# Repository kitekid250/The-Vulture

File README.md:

# The-Vulture
Work done on the robotic Vulture for Dana 147

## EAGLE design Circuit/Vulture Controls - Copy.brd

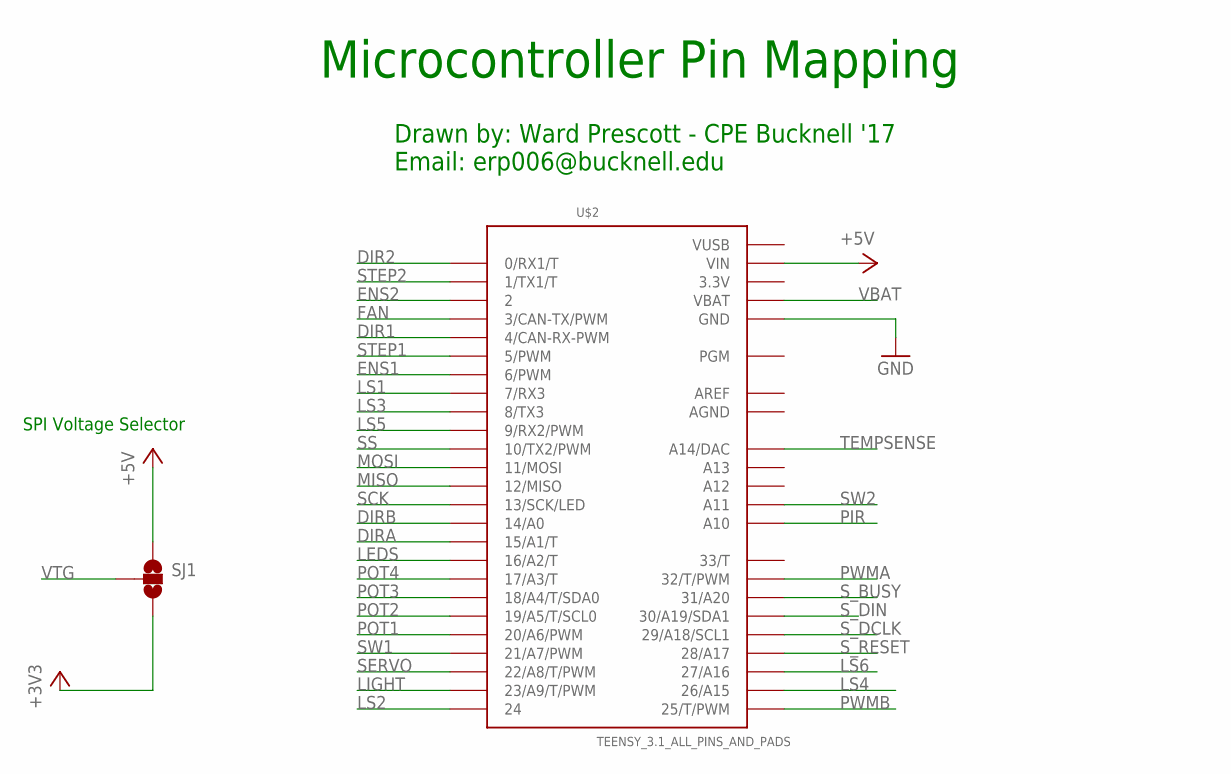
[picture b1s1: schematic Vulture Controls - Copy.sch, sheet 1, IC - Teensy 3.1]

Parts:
SJ1: JUMPER-PAD-3-NOFULL_BOX_SILK; PAD-JUMPER-3-NO_YES_SILK_FULL_BOX
U$2: TEENSY_3.1_ALL_PINS_AND_PADS; TEENSY_3.1_ALLPINS

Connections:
3.3V: U$2.3.3V, U$2.3.3V1 (3.3V), U$2.3.3V2 (3.3V)
+3V3: SJ1.3; also elsewhere on the board
+5V: SJ1.1, U$2.VIN; also elsewhere on the board
AGND: U$2.AGND
AREF: U$2.AREF
DIR1: U$2.4 (4/CAN-RX-PWM); also elsewhere on the board
DIR2: U$2.0 (0/RX1/T); also elsewhere on the board
DIRA: U$2.15/A1 (15/A1/T); also elsewhere on the board
DIRB: U$2.14/A0; also elsewhere on the board
ENS1: U$2.6 (6/PWM); also elsewhere on the board
ENS2: U$2.2; also elsewhere on the board
FAN: U$2.3 (3/CAN-TX/PWM); also elsewhere on the board
GND: U$2.GND, U$2.GND1 (GND), U$2.GND2 (GND); also elsewhere on the board
LEDS: U$2.16/A2 (16/A2/T); also elsewhere on the board
LIGHT: U$2.23/A9 (23/A9/T/PWM); also elsewhere on the board
LS1: U$2.7 (7/RX3); also elsewhere on the board
LS2: U$2.24; also elsewhere on the board
LS3: U$2.8 (8/TX3); also elsewhere on the board
LS4: U$2.26 (26/A15); also elsewhere on the board
LS5: U$2.9 (9/RX2/PWM); also elsewhere on the board
LS6: U$2.27 (27/A16); also elsewhere on the board
MISO: U$2.12 (12/MISO); also elsewhere on the board
MOSI: U$2.11 (11/MOSI); also elsewhere on the board
PIR: U$2.A10; also elsewhere on the board
POT1: U$2.20/A6 (20/A6/PWM); also elsewhere on the board
POT2: U$2.19/A5 (19/A5/T/SCL0); also elsewhere on the board
POT3: U$2.18/A4 (18/A4/T/SDA0); also elsewhere on the board
POT4: U$2.17/A3 (17/A3/T); also elsewhere on the board
PWMA: U$2.32 (32/T/PWM); also elsewhere on the board
PWMB: U$2.25 (25/T/PWM); also elsewhere on the board
SCK: U$2.13 (13/SCK/LED); also elsewhere on the board
SERVO: U$2.22/A8 (22/A8/T/PWM); also elsewhere on the board
SS: U$2.10 (10/TX2/PWM); also elsewhere on the board
STEP1: U$2.5 (5/PWM); also elsewhere on the board
STEP2: U$2.1 (1/TX1/T); also elsewhere on the board
SW1: U$2.21/A7 (21/A7/PWM); also elsewhere on the board
SW2: U$2.A11; also elsewhere on the board
S_BUSY: U$2.31 (31/A20); also elsewhere on the board
S_DCLK: U$2.29 (29/A18/SCL1); also elsewhere on the board
S_DIN: U$2.30 (30/A19/SDA1); also elsewhere on the board
S_RESET: U$2.28 (28/A17); also elsewhere on the board
TEMPSENSE: U$2.A14 (A14/DAC); also elsewhere on the board
VBAT: U$2.VBAT; also elsewhere on the board
VTG: SJ1.2; also elsewhere on the board
VUSB: U$2.VUSB

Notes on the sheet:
Microcontroller Pin Mapping
Drawn by: Ward Prescott - CPE Bucknell '17 Email: erp006@bucknell.edu
SPI Voltage Selector

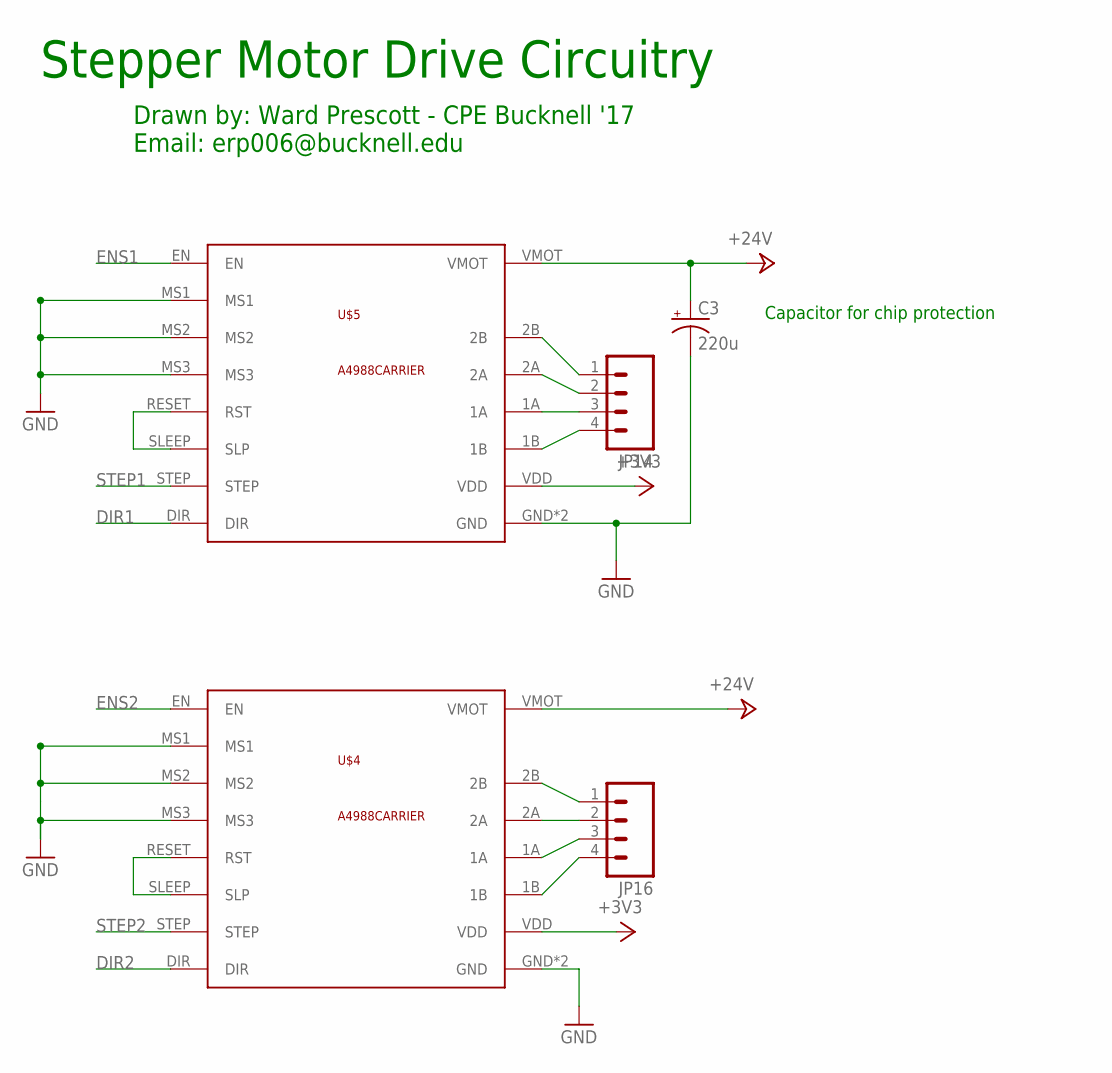
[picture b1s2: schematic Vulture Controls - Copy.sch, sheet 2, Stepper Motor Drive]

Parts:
C3: 220u; CPOL-RADIAL-1000UF-25V
JP14, JP16: M04POLAR_LOCK; MOLEX-1X4_LOCK
U$4, U$5: A4988CARRIER

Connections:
+3V3: U$4.VDD, U$5.VDD; also elsewhere on the board
+24V: C3.+, U$4.VMOT, U$5.VMOT; also elsewhere on the board
DIR1: U$5.DIR; also elsewhere on the board
DIR2: U$4.DIR; also elsewhere on the board
ENS1: U$5.EN; also elsewhere on the board
ENS2: U$4.EN; also elsewhere on the board
GND: C3.-, U$4.GND, U$4.GND2 (GND), U$4.MS1, U$4.MS2, U$4.MS3, U$5.GND, U$5.GND2 (GND), U$5.MS1, U$5.MS2, U$5.MS3; also elsewhere on the board
unnamed: JP14.1, U$5.2B
unnamed: JP14.2, U$5.2A
unnamed: JP14.3, U$5.1A
unnamed: JP14.4, U$5.1B
unnamed: JP16.1, U$4.2B
unnamed: JP16.2, U$4.2A
unnamed: JP16.3, U$4.1A
unnamed: JP16.4, U$4.1B
unnamed: U$5.RESET (RST), U$5.SLEEP (SLP)
unnamed: U$4.RESET (RST), U$4.SLEEP (SLP)
STEP1: U$5.STEP; also elsewhere on the board
STEP2: U$4.STEP; also elsewhere on the board

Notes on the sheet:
Capacitor for chip protection
Stepper Motor Drive Circuitry
Drawn by: Ward Prescott - CPE Bucknell '17 Email: erp006@bucknell.edu

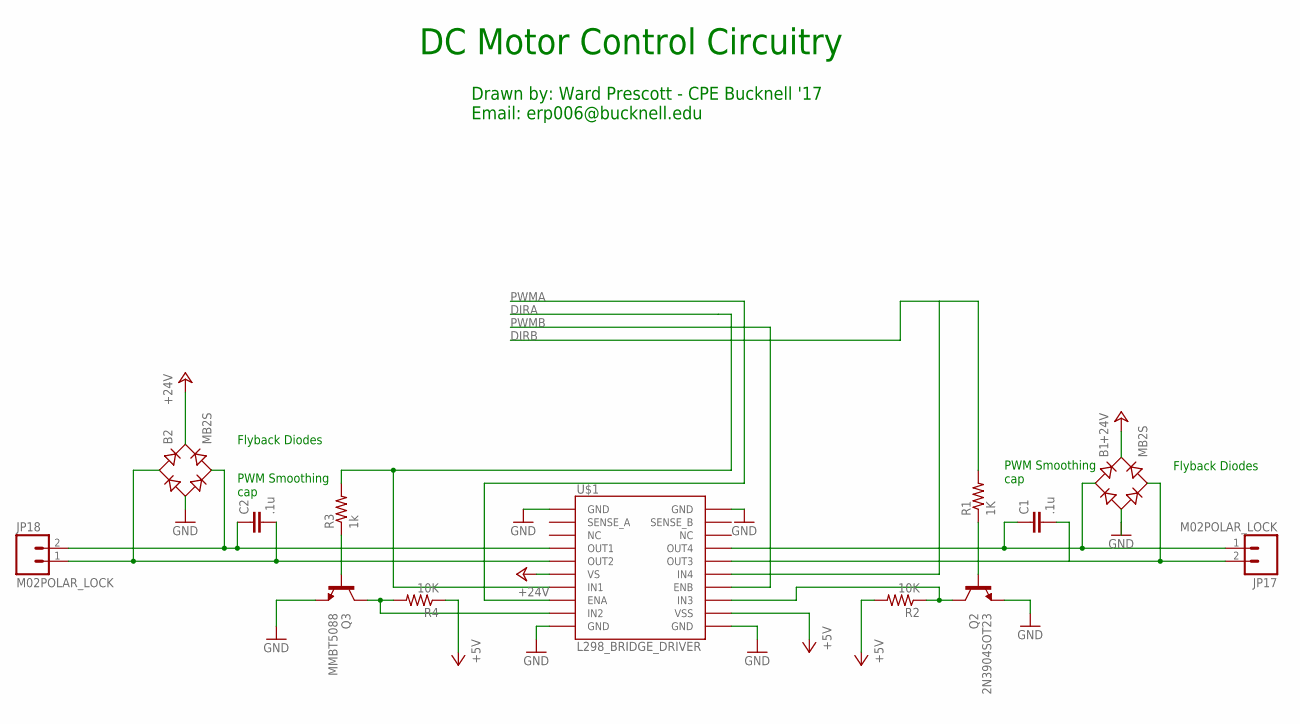
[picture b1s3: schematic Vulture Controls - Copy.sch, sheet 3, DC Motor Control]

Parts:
B1, B2: MB2S; SOIC-4
C1, C2: .1u; 1210
JP17, JP18: M02POLAR_LOCK; MOLEX-1X2_LOCK
Q2: 2N3904SOT23; SOT23
Q3: MMBT5088; SOT23
R1: 1K; 0805
R2, R4: 10K; 0603-RES
R3: 1k; 0805
U$1: L298_BRIDGE_DRIVER; POWERSO20

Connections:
+5V: R2.2, R4.1, U$1.12 (VSS); also elsewhere on the board
+24V: B1.+, B2.+, U$1.6 (VS); also elsewhere on the board
DIRA: R3.2, U$1.7 (IN1); also elsewhere on the board
DIRB: R1.2, U$1.15 (IN4); also elsewhere on the board
GND: B1.-, B2.-, Q2.2 (E), Q3.2 (E), U$1.1 (GND), U$1.10 (GND), U$1.11 (GND), U$1.20 (GND), U$1.P$1 (GND); also elsewhere on the board
unnamed: B2.~2 (AC2), C2.1, JP18.2, U$1.4 (OUT1)
unnamed: B2.~1 (AC1), C2.2, JP18.1, U$1.5 (OUT2)
unnamed: B1.~1 (AC1), C1.1, JP17.1, U$1.17 (OUT4)
unnamed: B1.~2 (AC2), C1.2, JP17.2, U$1.16 (OUT3)
unnamed: Q2.1 (B), R1.1
unnamed: Q2.3 (C), R2.1, U$1.13 (IN3)
unnamed: Q3.1 (B), R3.1
unnamed: Q3.3 (C), R4.2, U$1.9 (IN2)
PWMA: U$1.8 (ENA); also elsewhere on the board
PWMB: U$1.14 (ENB); also elsewhere on the board

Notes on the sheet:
Flyback Diodes
PWM Smoothing cap
DC Motor Control Circuitry
Drawn by: Ward Prescott - CPE Bucknell '17 Email: erp006@bucknell.edu

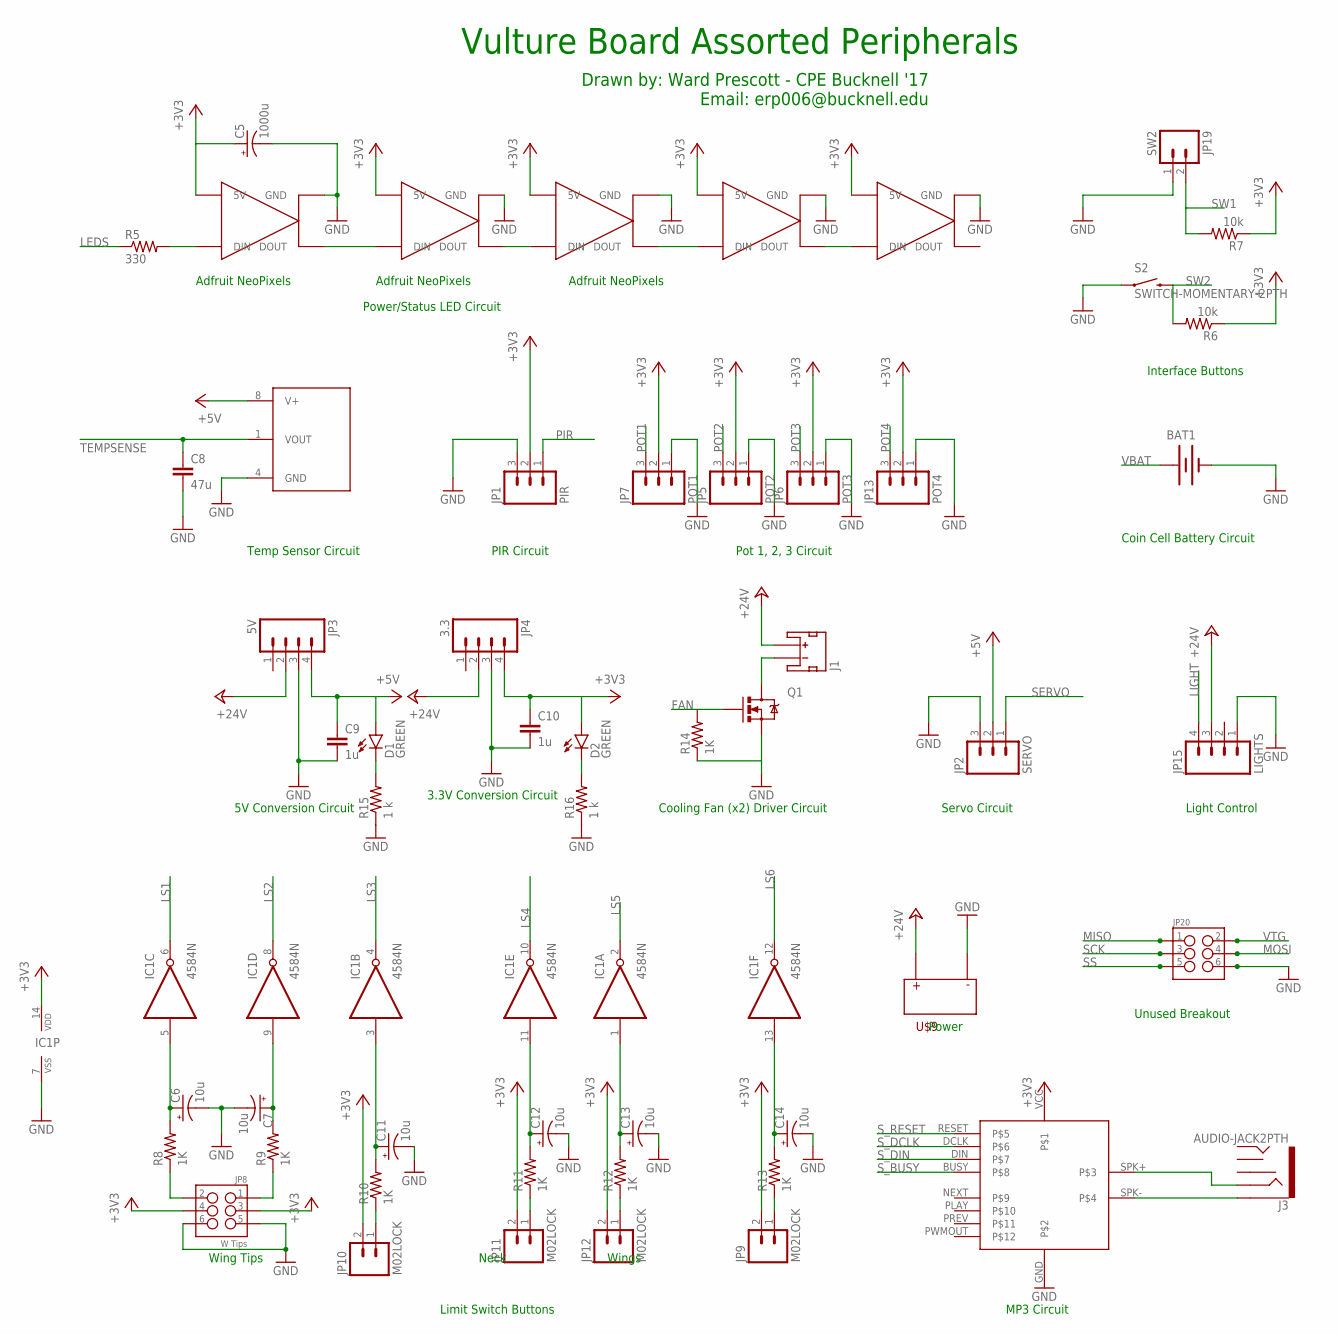
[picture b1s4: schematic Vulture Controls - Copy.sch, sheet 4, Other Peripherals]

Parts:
BAT1: BATTERY20PTH; BATTCOM_20MM_PTH
C5: 1000u; PANASONIC_G
C6, C7, C11, C12, C13, C14: 10u; PANASONIC_C
C8: 47u; 1206
C9, C10: 1u; 1206
D1, D2: GREEN; LED-1206
IC1: 4584N; DIL14
J1: JST_2MM_MALE; JST-2-SMD
J3: AUDIO-JACK2PTH; AUDIO-JACK
JP1: PIR; 1X03_LOCK_LONGPADS
JP2: SERVO; 1X03_LOCK_LONGPADS
JP3: 5V; 1X04_LOCK
JP4: 3.3; 1X04_LOCK
JP5: POT2; 1X03_LOCK_LONGPADS
JP6: POT3; 1X03_LOCK_LONGPADS
JP7: POT1; 1X03_LOCK_LONGPADS
JP8: W Tips; 2X3_POGO
JP9, JP10, JP11, JP12: M02LOCK; 1X02_LOCK
JP13: POT4; 1X03_LOCK_LONGPADS
JP15: LIGHTS; MOLEX-1X4_LOCK
JP19: SW2; 1X02_LOCK
JP20: M03X2POGO_PINS; 2X3_POGO
Q1: SSM3K329R,LF; SOT323
R5: 330; 0603-RES
R6, R7: 10k; 0603-RES
R8, R9, R10, R11, R12, R13, R14: 1K; 0805
R15, R16: 1 k; 0805
S2: SWITCH-MOMENTARY-2PTH; TACTILE-PTH
U$3: LM34; SO08
U$6, U$7, U$8, U$10, U$11: NEOPIXEL_THT
U$9: CONN_HDR_2POS_7.5MM_R/A_SLDR; MOLEXPOWER
U$12: WTV020SD-BRKOUT; WTVO20SD-BRKKOUT

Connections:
+3V3: C5.+, C10.1, D2.A, IC1.14 (VDD), JP1.2, JP4.4, JP5.2, JP6.2, JP7.2, JP8.P$3 (3), JP8.P$4 (4), JP9.2, JP10.2, JP11.2, JP12.2, JP13.2, R6.1, R7.1, U$6.5V, U$7.5V, U$8.5V, U$10.5V, U$11.5V, U$12.VCC; also elsewhere on the board
+5V: C9.1, D1.A, JP2.2, JP3.4, U$3.8 (V+); also elsewhere on the board
+24V: J1.2 (+), JP3.2, JP4.2, JP15.3, U$9.P$1, U$9.P$2; also elsewhere on the board
FAN: Q1.1 (G), R14.2; also elsewhere on the board
GND: BAT1.2 (-), C5.-, C6.-, C7.-, C8.2, C9.2, C10.2, C11.-, C12.-, C13.-, C14.-, IC1.7 (VSS), JP1.3, JP2.3, JP3.3, JP4.3, JP5.1, JP6.1, JP7.1, JP8.P$5 (5), JP8.P$6 (6), JP13.1, JP15.1, JP19.1, JP20.P$6 (6), Q1.2 (S), R14.1, R15.1, R16.1, S2.1, U$3.4 (GND), U$6.GND, U$7.GND, U$8.GND, U$9.P$3, U$9.P$4, U$10.GND, U$11.GND, U$12.GND; also elsewhere on the board
LEDS: R5.1; also elsewhere on the board
LIGHT: JP15.4; also elsewhere on the board
LS1: IC1.6 (O); also elsewhere on the board
LS2: IC1.8 (O); also elsewhere on the board
LS3: IC1.4 (O); also elsewhere on the board
LS4: IC1.10 (O); also elsewhere on the board
LS5: IC1.2 (O); also elsewhere on the board
LS6: IC1.12 (O); also elsewhere on the board
MISO: JP20.P$1 (1); also elsewhere on the board
MOSI: JP20.P$4 (4); also elsewhere on the board
N1: C6.+, IC1.5 (I), R8.2
N2: C7.+, IC1.9 (I), R9.2
N3: C11.+, IC1.3 (I), R10.2
N5: C13.+, IC1.1 (I), R12.2
N6: C14.+, IC1.13 (I), R13.2
unnamed: C12.+, IC1.11 (I), R11.2
unnamed: JP10.1, R10.1
unnamed: JP11.1, R11.1
unnamed: JP12.1, R12.1
unnamed: U$6.DOUT, U$7.DIN
unnamed: U$8.DOUT, U$10.DIN
unnamed: R5.2, U$6.DIN
unnamed: U$7.DOUT, U$8.DIN
unnamed: J1.1 (-), Q1.3 (D)
unnamed: JP8.P$2 (2), R8.1
unnamed: JP8.P$1 (1), R9.1
unnamed: JP9.1, R13.1
unnamed: U$10.DOUT, U$11.DIN
unnamed: J3.SLEEVE, U$12.SPK-
unnamed: J3.RING, U$12.SPK+
unnamed: D1.C, R15.2
unnamed: D2.C, R16.2
PIR: JP1.1; also elsewhere on the board
POT1: JP7.3; also elsewhere on the board
POT2: JP5.3; also elsewhere on the board
POT3: JP6.3; also elsewhere on the board
POT4: JP13.3; also elsewhere on the board
SCK: JP20.P$3 (3); also elsewhere on the board
SERVO: JP2.1; also elsewhere on the board
SS: JP20.P$5 (5); also elsewhere on the board
SW1: JP19.2, R7.2; also elsewhere on the board
SW2: R6.2, S2.3 (2); also elsewhere on the board
S_BUSY: U$12.BUSY; also elsewhere on the board
S_DCLK: U$12.DCLK; also elsewhere on the board
S_DIN: U$12.DIN; also elsewhere on the board
S_RESET: U$12.RESET; also elsewhere on the board
TEMPSENSE: C8.1, U$3.1 (VOUT); also elsewhere on the board
VBAT: BAT1.1 (+); also elsewhere on the board
VTG: JP20.P$2 (2); also elsewhere on the board

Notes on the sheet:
5V Conversion Circuit
Cooling Fan (x2) Driver Circuit
Temp Sensor Circuit
PIR Circuit
Servo Circuit
Pot 1, 2, 3 Circuit
Power/Status LED Circuit
MP3 Circuit
Limit Switch Buttons
Interface Buttons
Coin Cell Battery Circuit
3.3V Conversion Circuit
Light Control
Vulture Board Assorted Peripherals
Drawn by: Ward Prescott - CPE Bucknell '17 Email: erp006@bucknell.edu
Wing Tips
Wings
Neck
Adfruit NeoPixels
Power
Unused Breakout

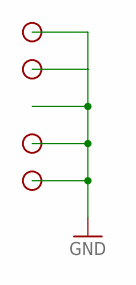
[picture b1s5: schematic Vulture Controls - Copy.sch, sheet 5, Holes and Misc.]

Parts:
STANDOFF1, STANDOFF2, STANDOFF4, STANDOFF6: STAND-OFF

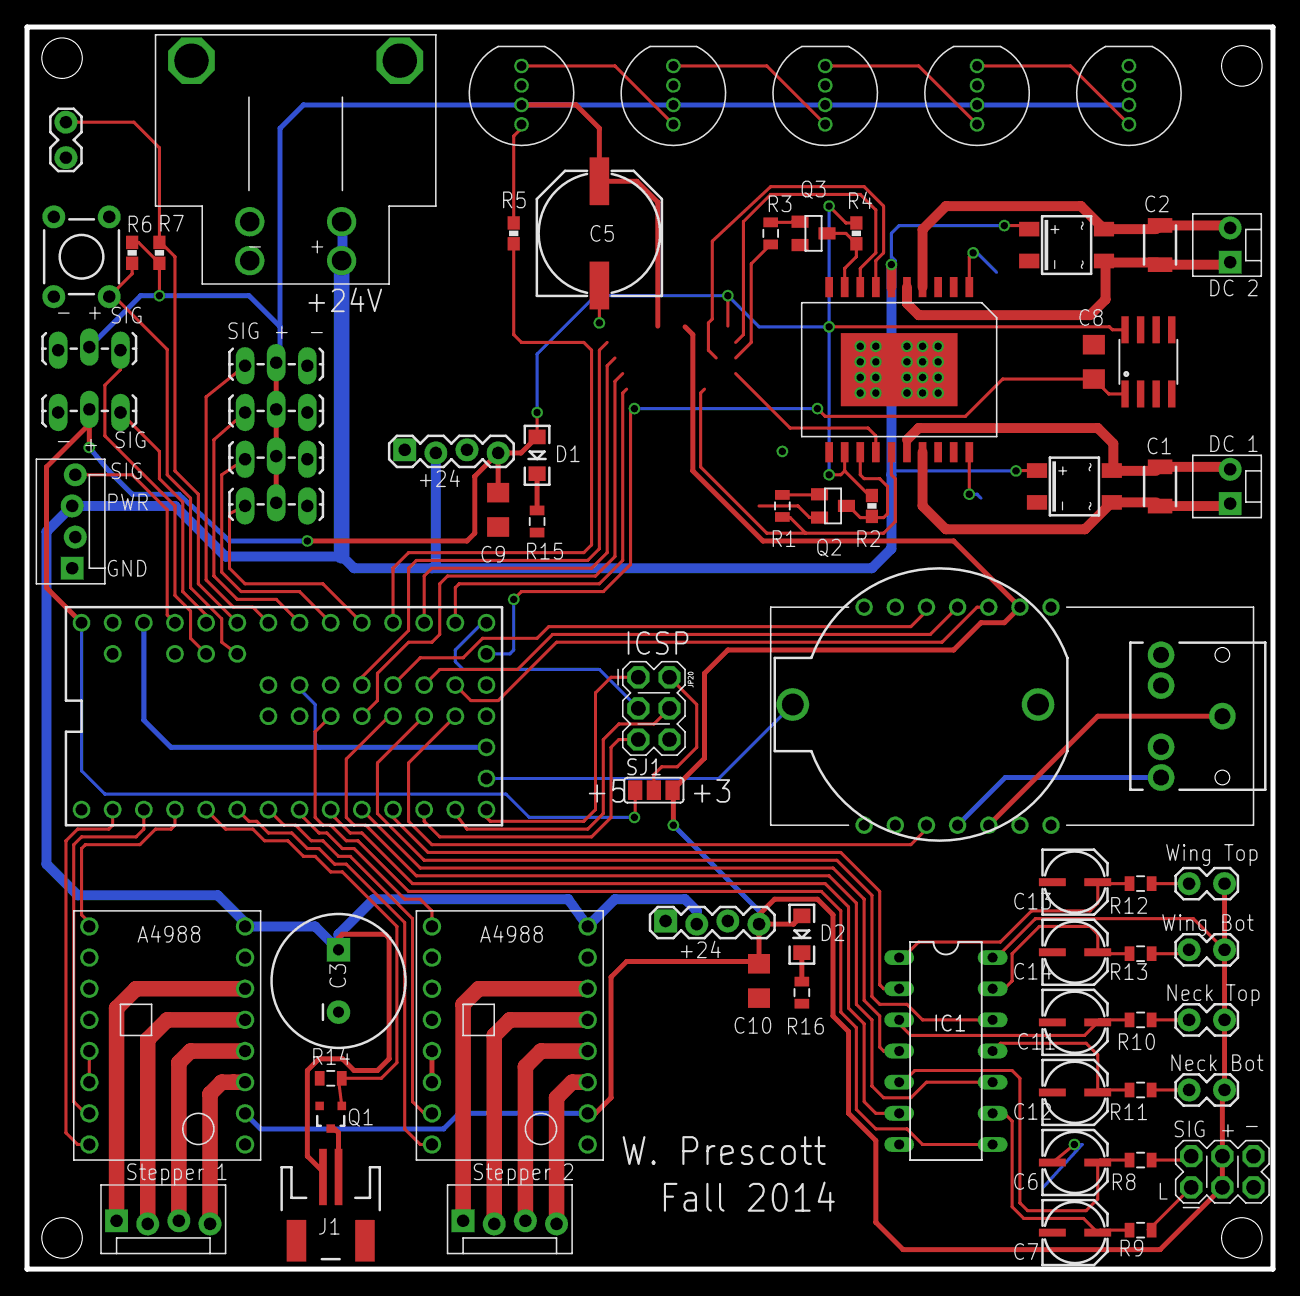
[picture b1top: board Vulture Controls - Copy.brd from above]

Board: 2 copper layers, 101.6 x 101.3 mm, 78 parts (0 on the bottom side), 83 nets.

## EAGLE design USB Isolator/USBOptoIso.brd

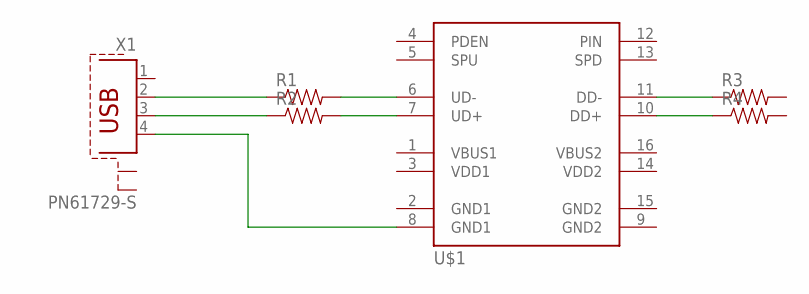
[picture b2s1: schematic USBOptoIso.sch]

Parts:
R1, R2, R3, R4: RESISTORKIT; AXIAL-0.3-KIT
U$1: ADUM4160; SO16W
X1: PN61729-S

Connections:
unnamed: R1.P$2 (2), U$1.6 (UD-)
unnamed: R2.P$2 (2), U$1.7 (UD+)
unnamed: R3.P$1 (1), U$1.11 (DD-)
unnamed: R4.P$1 (1), U$1.10 (DD+)
unnamed: R1.P$1 (1), X1.2
unnamed: R2.P$1 (1), X1.3
unnamed: U$1.8 (GND1), X1.4

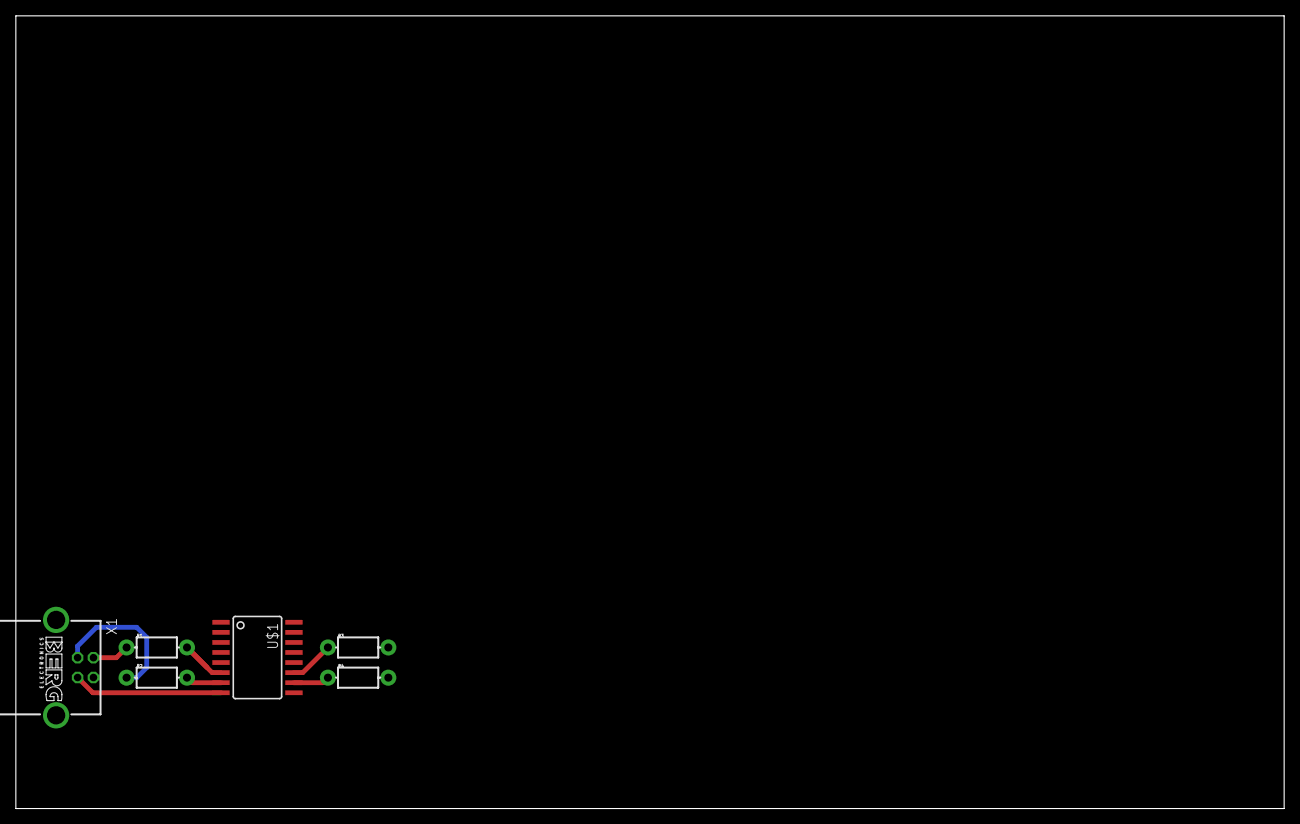
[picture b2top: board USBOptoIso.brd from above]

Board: 2 copper layers, 160.0 x 100.0 mm, 6 parts (0 on the bottom side), 7 nets.

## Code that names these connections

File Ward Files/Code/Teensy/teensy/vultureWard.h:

#ifndef GUARD
#define GUARD
#include <Time.h>
#define DIR1 0
#define STEP1 1
#define ENS1 2
#define FAN 3
#define DIR2 4
#define STEP2 5
#define ENS2 6
#define LS2 7
#define LS4 8
#define LS6 9
#define W_SS 10
#define W_MOSI 11
#define W_MISO 12
#define W_SCK 13
#define DIRB 14
#define DIRA 15
#define LEDS 16
#define POT4 A3
#define POT3 A4
#define POT2 A5
#define POT1 A6
#define SW2 21
#define SERVO 22
#define LIGHT 23
#define LS1 24
#define PWMB 25
#define LS3 26
#define LS5 27
#define S_RESET 28
#define S_DCLK 29
#define S_DIN 30
#define S_BUSY 31
#define PWMA 32
#define PIR A10
#define SW1 A11
#define TEMP A14

struct DCMotor constructDCMotor(int, int , int , int , int , int , int ,  void (*)());
struct DCMotor calibrate(struct DCMotor);
bool PIRRead(void);
void setupPins();
void refreshWatchDog();
void setupWatchDog();
float stdDev(float[], float, int);
float mean(float[], int);
float returnTemperature();
void setupClock();
time_t getTeensy3Time();
time_t timeDelta(time_t, time_t);



struct DCMotor {
  int rampUp;
  int rampDn;
  float speedPer;
  int desiredPos;
  int dir;
  volatile int rampUpCounter = 0;
  volatile int rampDnCounter = 0;
  int errorVal = 0;
  int upperLim;
  int lowerLim;
  int PotPin;
  int DirPin;
  int PwmPin;
  int LSUpperPin;
  int LSLowerPin;
  int expectedTop;
  int expectedBottom;
  void (*refresh)();
  int flag;
};


class CoolingFan {
public:
  bool isOn;
  char mode;
  void autoRegulate(void);
private:
  int controlPin;
  int temperaturePin;
};




#endif

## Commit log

2015-04-28 Bulk Commit
    All the files. I'll work through this later.
2015-04-28 Cleaning.
2015-05-03 Added Neck Homing
    Using a more simple procedure than I'd hoped, the neck can now home
    itself on the final motion. Other homing mechanisms to come.
2015-05-03 More Debugging, Cycle Counter
    Cycle counter added to aid in testing. It counts the cycles, duh.
    More output was moved to debug only to make the serial terminal a bit
    cleaner under normal operation. Still have to hunt down a few things
    though, I suspect they're hidden in the back files.
2015-05-15 Cleaned Up Directory
    Added a few mechanical parts too.
2015-05-24 Added Front Panel 2Ds
2015-05-24 Reduced LED Brightness
2015-05-25 Tweaked 3rd Motion Timing, Commented out Wings
2015-09-29 Vulture Rollout V2
    Fixed the original problem with the wings which required a bit of code
    updating.
2015-09-29 More Rollout V2
    Forgot to save a file before committing last time...
2015-12-22 Typical Backup

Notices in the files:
parts and their libraries:
SparkFun-PowerIC: Licensing: Creative Commons ShareAlike 4.0 International - https://creativecommons.org/licenses/by-sa/4.0
